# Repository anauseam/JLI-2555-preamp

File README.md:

# JLI-2555-tin-can-mic

A unprofessional "Mid"-Fi mic using a JLI 2555, meant to be housed in a tin can.

## Specs

Output voltage is designed to output a commercial level line signal via a TS connection.

All the components were designed to be purely through hole and non-obsolete, thus limiting the choices drastically.

If you would like a circuit that you can order pre made refer to the [WIP] Repo.

## Notes / Known issues

Because the potentiometer is DC biased, when the potentiometer collects dust years down the road there will be a scratching nose when turning the knob. Given that this is a literal mic housed in a tin can, I can accept this fact

Yes the entire circuit is running off of a 9v. This makes things as simple as possible, perfect for a proof of concept tin can microphone. Reasons for the unipolar supply:

- Adding a bipolar supply (two batteries) would introduce a new array of issues (e.g. uneven battery drain, size)

The biggest issue (IMO) is the OPA134 itself. Although it does have an excellent noise floor compared to standard op amps, compared a something like the OPA1642, or a proper discrete JFET, it has a noise floor of about 12.45 nV/sqrt(Hz) when considering the op amp's voltage noise and the voltage noise from the affect of the op amp's current noise and 1G resistor.

## TODO

Current the PCB is haphazardly connected, a proper layout will be completed once testing of the original circuit is done.

I will probably create a proper pcb with SMT

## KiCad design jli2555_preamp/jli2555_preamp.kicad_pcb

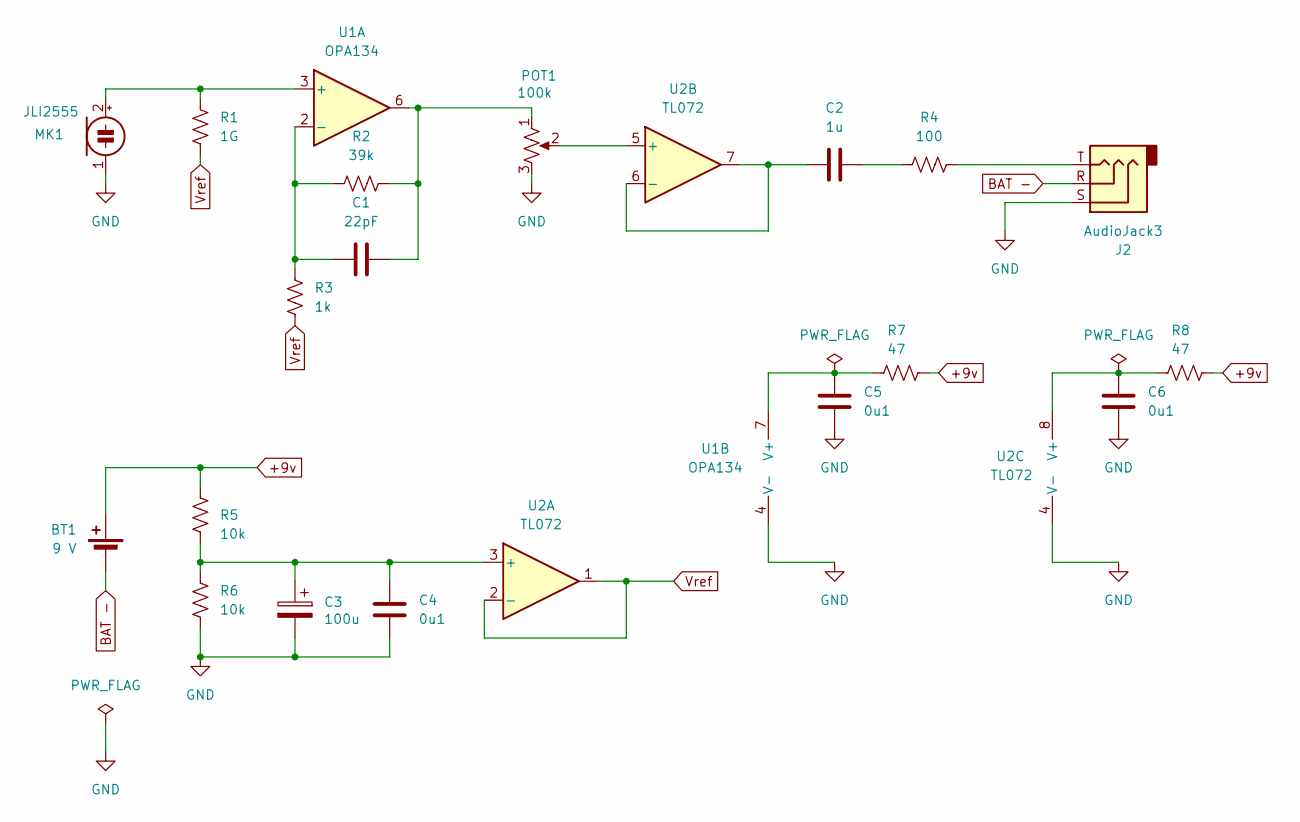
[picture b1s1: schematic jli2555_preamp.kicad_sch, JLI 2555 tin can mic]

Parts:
BT1: 9 V; BatteryHolder_MPD_BA9VPC_1xPP3
C1: 22pF; C_Disc_D5.0mm_W2.5mm_P2.50mm
C2: 1u; C_Rect_L7.2mm_W4.5mm_P5.00mm_FKS2_FKP2_MKS2_MKP2
C3: 100u; CP_Radial_D6.3mm_P2.50mm
C4: 0u1; C_Disc_D5.0mm_W2.5mm_P5.00mm
C5, C6: 0u1; C_Disc_D5.0mm_W2.5mm_P2.50mm
J2: AudioJack3; Jack_3.5mm_CUI_SJ1-3513N_Horizontal
MK1: JLI2555; SolderWire-0.1sqmm_1x02_P3.6mm_D0.4mm_OD1mm
POT1: 100k; Potentiometer_Alps_RK09Y11_Single_Horizontal
R1: 1G; R_Axial_DIN0207_L6.3mm_D2.5mm_P10.16mm_Horizontal
R2: 39k; R_Axial_DIN0207_L6.3mm_D2.5mm_P10.16mm_Horizontal
R3: 1k; R_Axial_DIN0207_L6.3mm_D2.5mm_P10.16mm_Horizontal
R4: 100; R_Axial_DIN0207_L6.3mm_D2.5mm_P10.16mm_Horizontal
R5, R6: 10k; R_Axial_DIN0207_L6.3mm_D2.5mm_P10.16mm_Horizontal
R7, R8: 47; R_Axial_DIN0207_L6.3mm_D2.5mm_P10.16mm_Horizontal
U1: OPA134; DIP-8_W7.62mm_Socket
U2: TL072; DIP-8_W7.62mm_Socket

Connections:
+9v: BT1.1 (+), R5.1, R7.2, R8.2
BAT -: BT1.2 (-), J2.R
GND: C3.2, C4.1, C5.1, C6.1, J2.S, MK1.1 (-), POT1.3, R6.2, U1.4 (V-), U2.4 (V-)
unnamed: C1.2, POT1.1, R2.2, U1.6
unnamed: C2.2, R4.1
unnamed: J2.T, R4.2
unnamed: MK1.2 (+), R1.1, U1.3 (+)
unnamed: C1.1, R2.1, R3.1, U1.2 (-)
unnamed: C5.2, R7.1, U1.7 (V+)
unnamed: C3.1, C4.2, R5.2, R6.1, U2.3 (+)
unnamed: POT1.2, U2.5 (+)
unnamed: C2.1, U2.6 (-), U2.7
unnamed: C6.2, R8.1, U2.8 (V+)
Vref: R1.2, R3.2, U2.1, U2.2 (-)

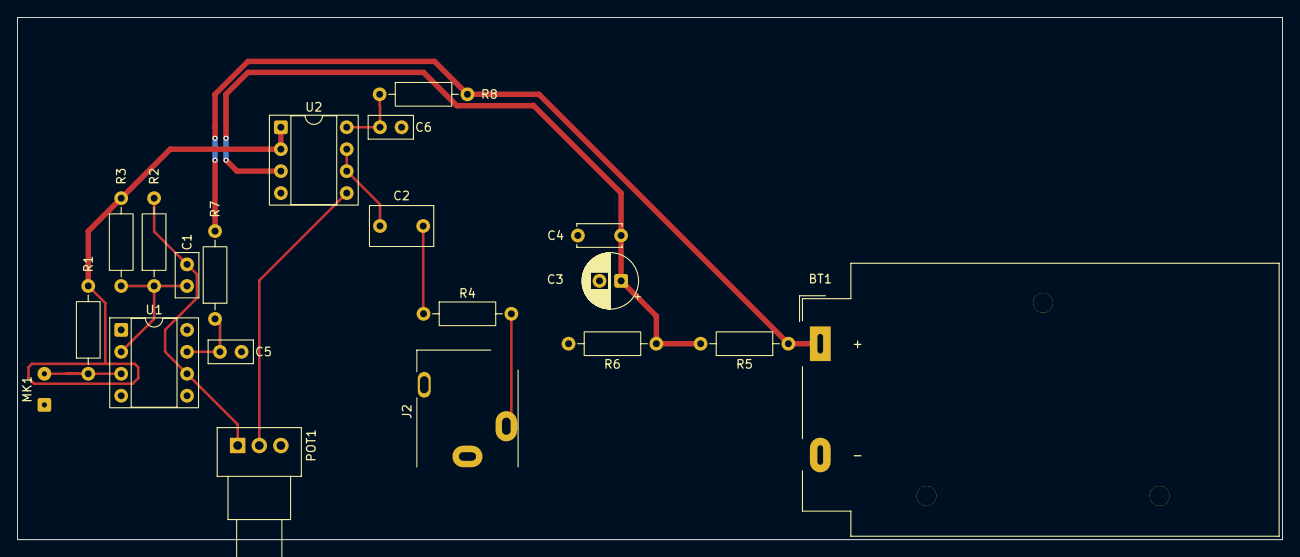
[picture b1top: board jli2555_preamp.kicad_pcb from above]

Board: 2 copper layers, 146.4 x 60.4 mm, 20 parts (0 on the bottom side), 14 nets.

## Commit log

2025-05-25 Add project files
2025-05-26 Finalize inital design of schematic
2025-11-07 Last version using USB power, JFET to op amp change
2025-11-12 Overhaul of the power supply, will now be a 9v supply for greater simplicity
